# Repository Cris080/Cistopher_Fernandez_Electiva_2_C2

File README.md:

# Cistopher_Fernandez_Electiva_2_C2

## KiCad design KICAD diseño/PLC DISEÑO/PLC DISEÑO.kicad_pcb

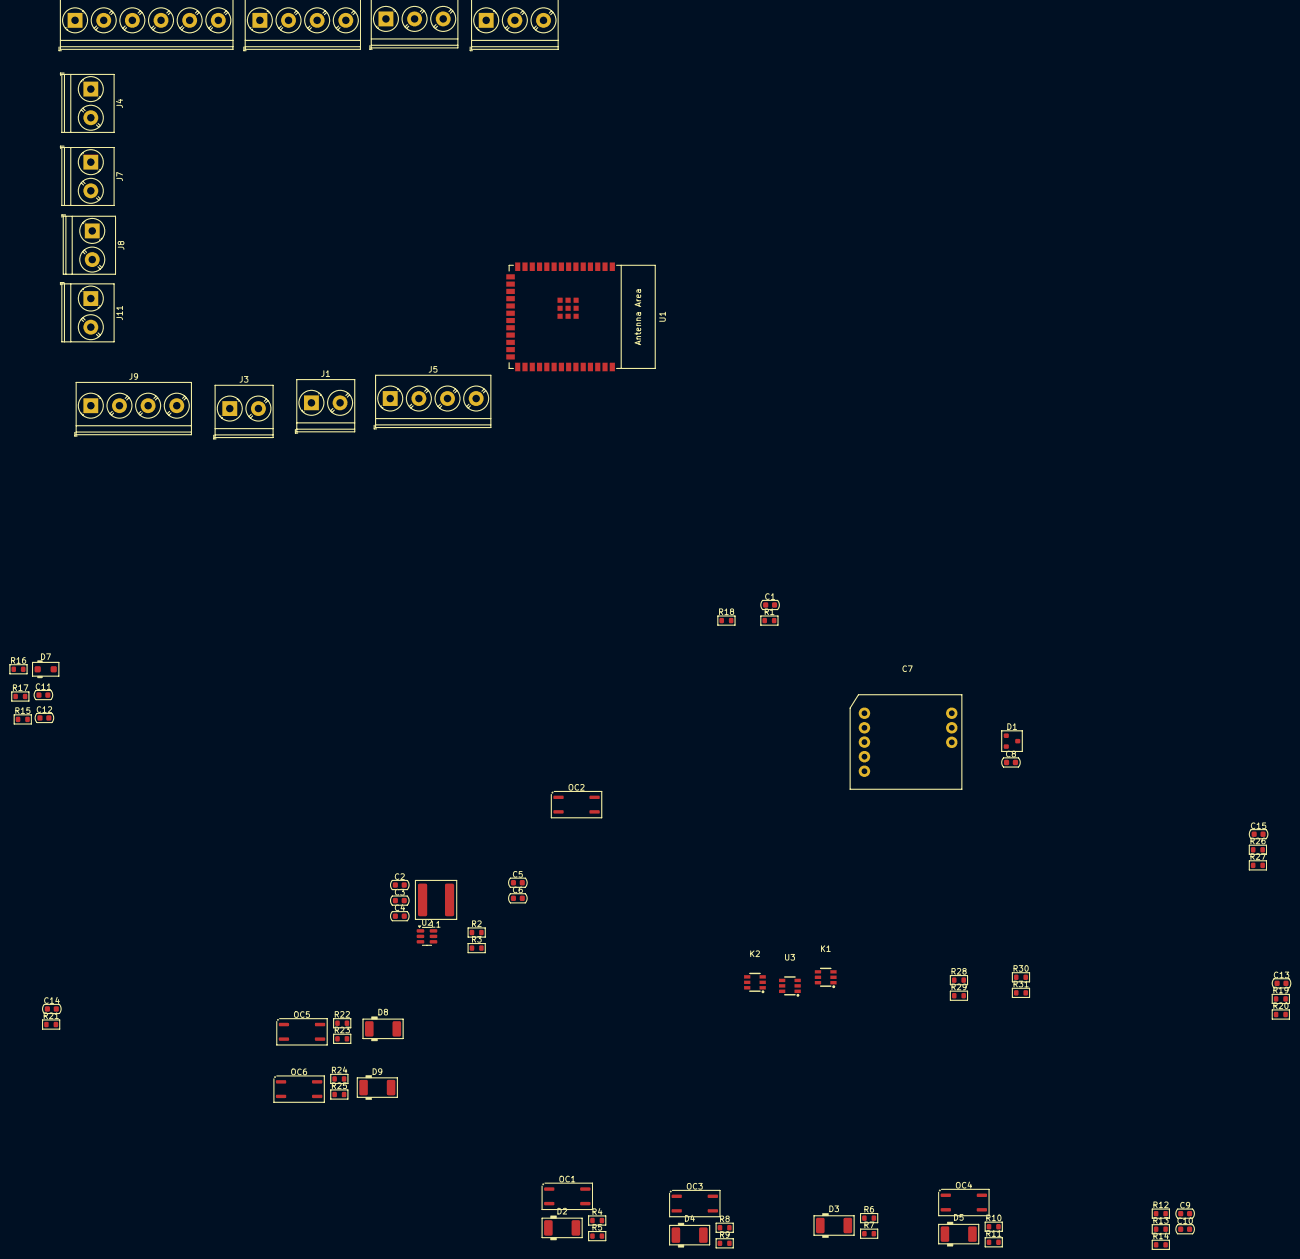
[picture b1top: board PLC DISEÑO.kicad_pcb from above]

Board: 2 copper layers, 78 parts (0 on the bottom side), 58 nets, no tracks yet.

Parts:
C1: 1u; C_0603_1608Metric
C2, C8, C9, C10, C11, C12, C13, C14, C15: C_0603; C_0603_1608Metric
C3, C4: 100pF; C_0603_1608Metric
C5, C6: 22uF; C_0603_1608Metric
C7: C2992406
D1: SM712; SOT-23
D2, D3, D4, D5, D8, D9: DL4007; D_MELF
D7: SMF24A; D_SOD-123F
J1, J3, J4, J7, J8, J11: Screw_Terminal_2_P5.00mm; TerminalBlock_Phoenix_PT-1,5-2-5.0-H_1x02_P5.00mm_Horizontal
J2, J5, J9: Screw_Terminal_4_P5.00mm; TerminalBlock_Phoenix_PT-1,5-4-5.0-H_1x04_P5.00mm_Horizontal
J6, J10: Screw_Terminal_3_P5.00mm; TerminalBlock_Phoenix_PT-1,5-3-5.0-H_1x03_P5.00mm_Horizontal
J14: Screw_Terminal_6_P5.00mm; TerminalBlock_Phoenix_PT-1,5-6-5.0-H_1x06_P5.00mm_Horizontal
K1, K2: SRA-24VDC-CL; SOT-23-6_L2.9-W1.6-P0.95-LS2.8-BR
L1: L_Iron; L_Bourns-SRN6028
OC1, OC2, OC3, OC4, OC5, OC6: LTV-357T; SO-4_4.4x3.9mm_P2.54mm
R1, R4, R5, R6, R7, R8, R9, R10, R11, R12, R13, R14, R15, R16, R17, R18, R19, R20, R21, R22, R23, R24, R25, R26, R27, R28, R29, R30, R31: R_0603; R_0603_1608Metric
R2, R3: 22k; R_0603_1608Metric
U1: ESP32-S3-WROOM-1
U2: AP63203WU; TSOT-23-6
U3: LK1802; SOT-23-6_L2.9-W1.6-P0.95-LS2.8-BR

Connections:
+3.3V: C4.1, C5.1, C6.1, C7.1 (VCC), C8.1, D1.2 (A2), L1.2, OC2.4, OC4.4, OC5.4, OC6.4, R1.1, R2.1, R5.1, R9.1, R12.1, R13.1, R16.1, R17.1, R18.1
/BOARD_NIRVARA/0.10Vin/0-10V: C15.1, R26.2, R27.1, U1.10 (GPIO17/U1TXD/ADC2_CH6)
/BOARD_NIRVARA/A032_IN1: C13.1, J2.2, R19.1, R20.2
/BOARD_NIRVARA/A420_IN1: C14.1, J2.3, R21.1, U1.23 (GPIO21)
/BOARD_NIRVARA/AOUT_010_1: C11.1, D7.1 (K), J6.1
/BOARD_NIRVARA/DRIVER_RS485/UART_IN: C7.3 (TXD), U1.21 (GPIO13/TOUCH13/ADC2_CH2/FSPIQ/FSPIIO7/S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)
/BOARD_NIRVARA/DRIVER_RS485/UART_OUT: C7.4 (RXD), U1.22 (GPIO14/TOUCH14/ADC2_CH3/FSPIWP/FSPIDQS/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)
/BOARD_NIRVARA/INPUT_NPN/NPN_input_1: OC1.4, R5.2, U1.5 (GPIO5/TOUCH5/ADC1_CH4)
/BOARD_NIRVARA/INPUT_NPN/NPN_input_2: OC3.4, R9.2, U1.6 (GPIO6/TOUCH6/ADC1_CH5)
/BOARD_NIRVARA/INPUT_PNP/PNP_input_1: OC2.3, R7.2, U1.7 (GPIO7/TOUCH7/ADC1_CH6)
/BOARD_NIRVARA/INPUT_PNP/PNP_input_2: OC4.3, R11.2, U1.12 (GPIO8/TOUCH8/ADC1_CH7/SUBSPICS1)
/BOARD_NIRVARA/Modulo_010/SCLK: R16.2, U1.18 (GPIO10/TOUCH10/ADC1_CH9/FSPICS0/FSPIIO4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)
/BOARD_NIRVARA/Modulo_010/SDA: R17.2, U1.17 (GPIO9/TOUCH9/ADC1_CH8/FSPIHD/SUBSPIHD)
/BOARD_NIRVARA/Modulo_in/input_1: OC5.3, R23.2, U1.37 (U0TXD/GPIO43/CLK_OUT1)
/BOARD_NIRVARA/Modulo_in/input_2: OC6.3, R25.2, U1.36 (U0RXD/GPIO44/CLK_OUT2)
/BOARD_NIRVARA/Modulo_out_420/ASLK: R13.2, U1.19 (GPIO11/TOUCH11/ADC2_CH0/FSPID/FSPIIO5/S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)
/BOARD_NIRVARA/Modulo_out_420/SDA: R12.2, U1.20 (GPIO12/TOUCH12/ADC2_CH1/FSPICLK/FSPIIO6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)
/BOARD_NIRVARA/NPN_IN_1: J7.1, R4.1
/BOARD_NIRVARA/NPN_IN_2: J7.2, R8.1
/BOARD_NIRVARA/Out_NPN/NPN-1: R28.1, U1.39 (GPIO1/TOUCH1/ADC1_CH0)
/BOARD_NIRVARA/Out_NPN/NPN-2: R29.1, U1.38 (GPIO2/TOUCH2/ADC1_CH1)
/BOARD_NIRVARA/Out_PNP/PNP-1: R30.1, U1.15 (GPIO3/TOUCH3/ADC1_CH2)
/BOARD_NIRVARA/Out_PNP/PNP-2: R31.1, U1.4 (GPIO4/TOUCH4/ADC1_CH3)
/BOARD_NIRVARA/PNP_IN_1: J4.1, R6.1
/BOARD_NIRVARA/PNP_IN_2: J4.2, R10.1
/BOARD_NIRVARA/RLY1_C: J14.2, K2.5
/BOARD_NIRVARA/RLY1_NC: J14.1, K2.2
/BOARD_NIRVARA/RLY1_NO: J14.3, K2.1
/BOARD_NIRVARA/RLY2_C: J14.5, K1.5
/BOARD_NIRVARA/RLY2_NC: J14.4, K1.2
/BOARD_NIRVARA/RLY2_NO: J14.6, K1.1
/BOARD_NIRVARA/RS485-A: C7.9 (A), J10.1
/BOARD_NIRVARA/RS485-B: C7.8 (B), J10.2
/BOARD_NIRVARA/RUN/STOP: J3.1, J11.1, R18.2, U1.29 (SPIIO7/GPIO36/FSPICLK/SUBSPICLK)
/BOARD_NIRVARA/Realy/RLY_1: U1.14 (GPIO20/U1CTS/ADC2_CH9/CLK_OUT1/USB_D+), U3.3 (1B)
/BOARD_NIRVARA/Realy/RLY_2: U1.13 (GPIO19/U1RTS/ADC2_CH8/CLK_OUT2/USB_D-), U3.4 (2B)
/BOARD_NIRVARA/in + 2: J5.3, R22.1, R24.1
/BOARD_NIRVARA/in - 1: D8.2 (A), J5.2, OC5.2
/BOARD_NIRVARA/in - 2: D9.2 (A), J5.4, OC6.2
GND: C1.2, C2.2, C5.2, C6.2, C9.2, C10.1, C11.2, C12.2, C14.2, D1.3 (Com), D2.2 (A), D3.2 (A), D4.2 (A), D5.2 (A), D7.2 (A), J1.2, J2.4, J3.2, J6.3, J10.3, J11.2, OC1.2, OC1.3, OC2.2, OC3.2, OC3.3, OC4.2, R3.2, R7.1, R11.1, R14.2, R21.2, R23.1, R25.1, U1.1 (GND), U1.40 (GND), U1.41 (GND), U2.4 (GND), U3.2 (E)
unnamed: C7.2 (GND), C8.2, D1.1 (A1)
unnamed: D2.1 (K), OC1.1, R4.2
unnamed: D3.1 (K), OC2.1, R6.2
unnamed: D4.1 (K), OC3.1, R8.2
unnamed: D5.1 (K), OC4.1, R10.2
unnamed: C13.2, R19.2
unnamed: D8.1 (K), OC5.1, R22.2
unnamed: D9.1 (K), OC6.1, R24.2
unnamed: C15.2, R27.2
unnamed: C1.1, R1.2, U1.3 (EN)
unnamed: C3.1, U2.6 (BST)
unnamed: C4.2, R2.2, R3.1, U2.1 (FB)
unnamed: C3.2, L1.1, U2.5 (SW)
unnamed: K2.4, U3.1 (1C)
unnamed: K1.4, U3.6 (2C)
unnamed: C9.1, R14.1
unnamed: C12.1, R15.1
VCC: C2.1, J1.1, K1.3, K2.3, U2.2 (EN), U2.3 (IN), U3.5 (COM)

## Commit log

2025-05-16 Ejemplo 1 git.txt
2025-05-16 ejemplo 2
2025-05-16 ejemplo 1.txt
2025-05-17 delete
2025-05-23 Resumen
2025-05-29 Tarea Freed y Solid
2025-06-06 Tarea semana 3
2025-06-13 Kicad diseño 1ra version
2025-06-21 Tarea 4
2025-07-04 SCH y FP C2992406
2025-07-16 Actualizacion
2025-07-16 Actualizacion estoy cansado jefe :)
2025-07-16 Nirvara actualization :>
2025-07-16 Actualizacion 20 :[
2025-07-30 uptade
